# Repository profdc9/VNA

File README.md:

This a project to create a Vector Network Analyzer based on the EU1KY antenna tuner that can be reconfigured for different needs.  This material is copyrighted by Daniel Marks (KW4TI) and licensed under the Creative Commons License CC-BY-SA 4.0.  The software is licensed under the zlib license.  These are open source licenses that permit commercial use, modification and redistribution with attribution, and require licensees to assume all risk for using the copyrighted materials.

Currently what is on this github are the Kicad files for the VNA and the software.  The software uses the "stm32duino" extension to the Arduino IDE.  The Arduino IDE can be downloaded from

https://www.arduino.cc/en/Main/Software

The stm32duino software can be installed using the instructions on the stm32duino web site

https://github.com/rogerclarkmelbourne/Arduino_STM32/wiki/Installation

which involves (at this time) downloading the git archive for the stm32duino and placing it under the "hardware" folder in your Arduino folder.

There are several Arduino libraries that are required for the SI5351A frequency synthesizer chip, ILI9341 TFT display module, and XPT2046 touchscreen controller.  These are provided for your use under the "libraries" directory of this archive, but may not be the most recent versions.  You could copy these directories into the "libraries" folder in your Arduino directory.

---------------------------------

The VNA may be used with or without a touchscreen.  If a touchscreen it used, it should be compiled with the "VNA_TOUCHSCREEN" defined in VNA.h.  If you do not have a touchscreen, you can ground the pin PB13 and it will start up without a touchscreen, only appearing a USB CDC serial port device.  You can then type "HELP" to see the list of commands.

The touchscreen used is a 2.8" touchscreen with a SPI interface to the ILI9341 and XPT2046.  These are commonly available at a low price.  To connect it to the SPI interface connector header "J1" on the board, use a 14 pin IDC ribbon cable.

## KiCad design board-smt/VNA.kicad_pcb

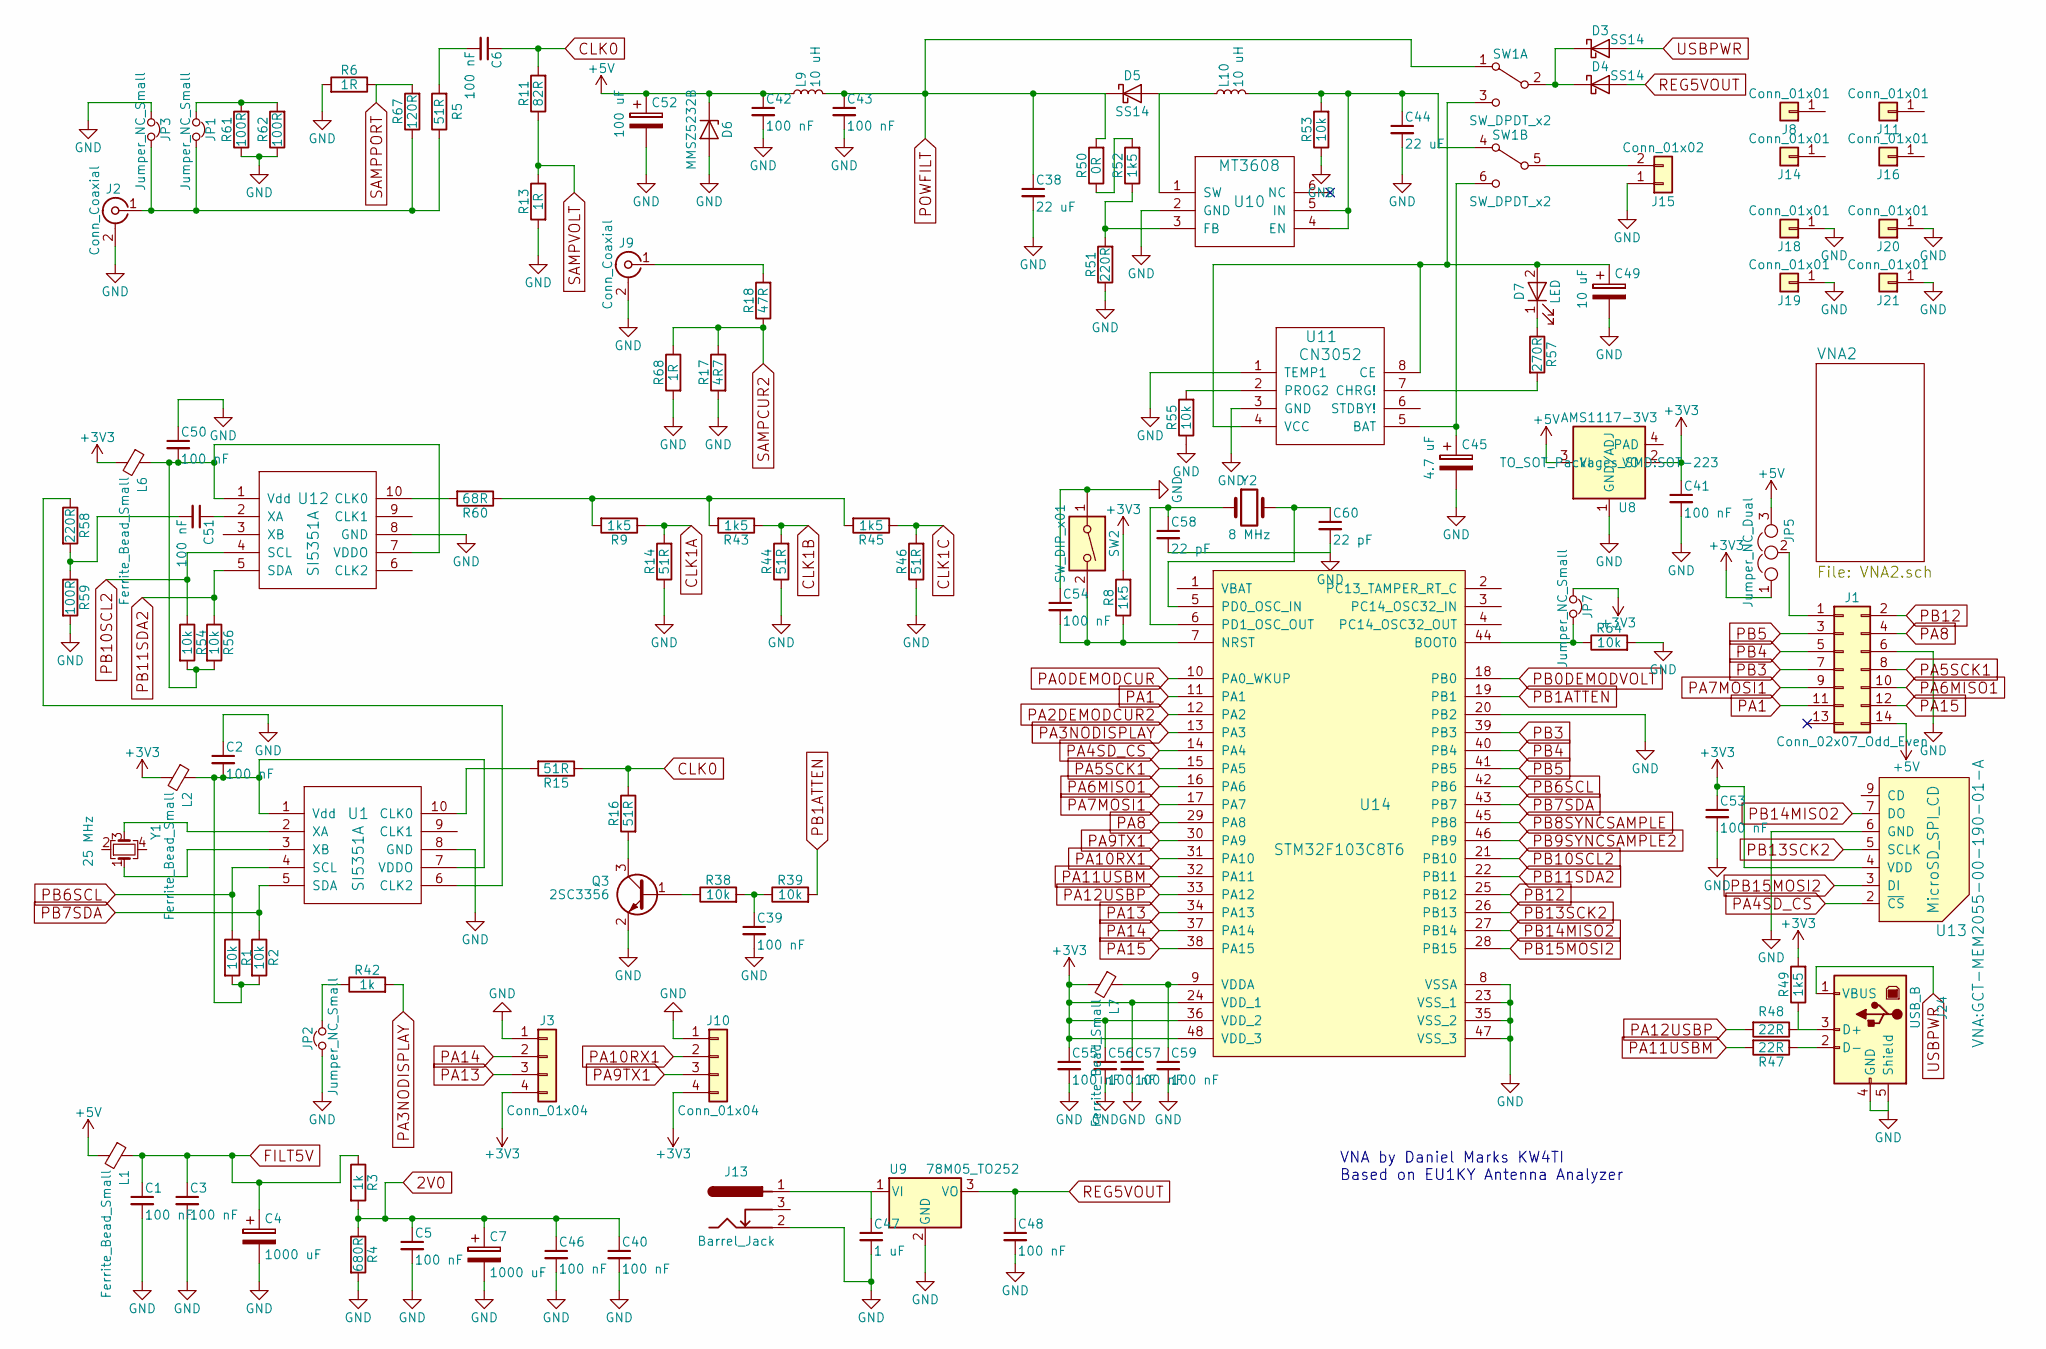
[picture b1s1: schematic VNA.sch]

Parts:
C1, C2, C3, C5, C6, C39, C40, C41, C42, C43, C46, C48, C50, C54, C55, C56, C57, C59: 100 nF; C_0805_HandSoldering; LCSC C49678
C4, C7: 1000 uF; CP_Elec_8x10.5
C38, C44: 22 uF; C_1210_HandSoldering
C45: 4.7 uF; CP_Elec_4x4.5
C47: 1 uF; C_0805_HandSoldering; LCSC C28323
C49: 10 uF; CP_Elec_4x4.5
C51, C53: 100 nF; C_0805_HandSoldering
C52: 100 uF; CP_Elec_4x4.5
C58, C60: 22 pF; C_0805_HandSoldering; LCSC C1804
D3, D4, D5: SS14; D_SMA; LCSC C2480
D6: MMSZ5232B; D_MiniMELF; LCSC C8062
D7: LED; LED_0805; LCSC C84256
J1: Conn_02x07_Odd_Even; Pin_Header_Straight_2x07_Pitch2.54mm
J2, J9: Conn_Coaxial; Amphenol_RF_SMA_132289
J3, J10: Conn_01x04; Pin_Header_Straight_1x04_Pitch2.54mm
J8, J11, J14, J16, J18, J19, J20, J21: Conn_01x01; 1pin
J13: Barrel_Jack; BARREL_JACK
J15: Conn_01x02; Molex_KK-6410-02_02x2.54mm_Straight
J24: USB_B
JP1, JP2, JP3, JP7: Jumper_NC_Small; Pin_Header_Straight_1x02_Pitch2.54mm
JP5: Jumper_NC_Dual; Pin_Header_Straight_1x03_Pitch2.54mm
L1, L2, L6, L7: Ferrite_Bead_Small; L_0805_HandSoldering; LCSC C1015
L9, L10: 10 uH; L_7.3x7.3_H4.5
Q3: 2SC3356; SOT-23; LCSC C9659
R1, R2, R38, R39, R53, R54, R55, R56, R64: 10k; R_0805_HandSoldering; LCSC C17414
R3, R42: 1k; R_0805_HandSoldering; LCSC C17513
R4: 680R; R_0805_HandSoldering; LCSC C17798
R5, R14, R15, R16, R44, R46: 51R; R_0805_HandSoldering; LCSC C17738
R6, R13, R68: 1R; R_0805_HandSoldering; LCSC C25271
R8, R9, R43, R45, R49, R52: 1k5; R_0805_HandSoldering; LCSC C4310
R11: 82R; R_0805_HandSoldering; LCSC C17841
R17: 4R7; R_0805_HandSoldering; LCSC C17675
R18: 47R; R_0805_HandSoldering; LCSC C17714
R47, R48: 22R; R_0805_HandSoldering; LCSC C17561
R50: 0R; R_0805_HandSoldering; LCSC C17477
R51, R58: 220R; R_0805_HandSoldering; LCSC C17557
R57: 270R; R_0805_HandSoldering; LCSC C17590
R59, R61, R62: 100R; R_0805_HandSoldering; LCSC C17408
R60: 68R; R_0805_HandSoldering; LCSC C17802
R67: 120R; R_0805_HandSoldering; LCSC C17437
SW1: SW_DPDT_x2; Molex_KK-6410-06_06x2.54mm_Straight
SW2: SW_DIP_x01; SW_PUSH_6mm
U1, U12: SI5351A; MSOP-10_3x3mm_Pitch0.5mm
U8: AMS1117-3V3; SOT-223; MPN LM1117; LCSC C6186
U9: 78M05_TO252; TO-252-3_TabPin2; LCSC C58069
U10: MT3608; SOT-23-6
U11: CN3052; TI_SO-PowerPAD-8
U13: MicroSD_SPI_CD; GCT-MEM2055-00-190-01-A
U14: STM32F103C8T6; LQFP-48_7x7mm_Pitch0.5mm; LCSC C8304
Y1: 25 MHz; Crystal_SMD_3225-4pin_3.2x2.5mm_HandSoldering; LCSC C9006
Y2: 8 MHz; Crystal_SMD_5032-2pin_5.0x3.2mm_HandSoldering; LCSC C115962

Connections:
2V0: C5.1, C7.1, C40.1, C46.1, R3.2, R4.1; also elsewhere on the board
+3V3: C41.1, C53.1, C55.1, C56.1, C57.1, J3.4, J10.4, JP5.1, JP7.1, L2.2, L6.2, L7.2, R8.2, R49.2, U8.2 (VO), U13.4 (VDD), U14.24 (VDD_1), U14.36 (VDD_2), U14.48 (VDD_3)
+5V: C42.1, C52.1, D6.1 (K), J1.14, JP5.3, L1.2, L9.1, U8.3 (VI)
CLK0: C6.1, R11.2, R15.1, R16.1
CLK1A: R9.1, R14.2; also elsewhere on the board
CLK1B: R43.1, R44.2; also elsewhere on the board
CLK1C: R45.1, R46.2; also elsewhere on the board
FILT5V: C1.1, C3.1, C4.1, L1.1, R3.1; also elsewhere on the board
GND: C1.2, C2.1, C3.2, C4.2, C5.2, C7.2, C38.2, C39.2, C40.2, C41.2, C42.2, C43.2, C44.2, C45.2, C46.2, C47.2, C48.2, C49.2, C50.1, C52.2, C53.2, C54.1, C55.2, C56.2, C57.2, C58.2, C59.2, C60.2, D6.2 (A), J1.6, J2.2 (Ext), J3.1, J9.2 (Ext), J10.1, J13.2, J15.1, J18.1, J19.1, J20.1, J21.1, J24.4 (GND), J24.5 (Shield), JP2.1, JP3.1, Q3.2 (E), R4.2, R6.2, R13.2, R14.1, R17.2, R44.1, R46.1, R51.1, R53.1, R55.1, R59.2, R61.1, R62.1, R64.2, R68.2, SW2.1, U1.8 (GND), U8.1 (GND/ADJ), U9.2 (GND), U10.2 (GND), U11.1 (TEMP1), U11.3 (GND), U12.8 (GND), U13.6 (GND), U14.8 (VSSA), U14.20 (PB2), U14.23 (VSS_1), U14.35 (VSS_2), U14.47 (VSS_3); also elsewhere on the board
unnamed: C2.2, L2.1, R1.2, R2.2, U1.1 (Vdd), U1.7 (VDDO)
unnamed: C6.2, R5.2
unnamed: C39.1, R38.2, R39.1
unnamed: C44.1, L10.2, R53.2, SW1.4 (A), U10.4 (EN), U10.5 (IN)
unnamed: C45.1, SW1.6 (C), U11.5 (BAT)
unnamed: C47.1, J13.1, U9.1 (VI)
unnamed: C49.1, D7.2 (A), SW1.3 (C), U11.4 (VCC), U11.8 (CE)
unnamed: C50.2, L6.1, R54.2, R56.2, U12.1 (Vdd), U12.7 (VDDO)
unnamed: C51.1, U12.2 (XA)
unnamed: C51.2, R58.2, R59.1
unnamed: C54.2, R8.1, SW2.2, U14.7 (NRST)
unnamed: C58.1, U14.6 (PD1_OSC_OUT), Y2.1
unnamed: C59.1, L7.1, U14.9 (VDDA)
unnamed: C60.1, U14.5 (PD0_OSC_IN), Y2.2
unnamed: D3.1 (K), D4.1 (K), SW1.2 (B)
unnamed: D5.2 (A), L10.1, U10.1 (SW)
unnamed: D7.1 (K), R57.1
unnamed: J1.1, JP5.2
unnamed: J2.1 (In), JP1.2, JP3.2, R5.1, R67.1
unnamed: J9.1 (In), R18.2
unnamed: J15.2, SW1.5 (B)
unnamed: J24.2 (D-), R47.1
unnamed: J24.3 (D+), R48.1, R49.1
unnamed: JP1.1, R61.2, R62.2
unnamed: JP2.2, R42.1
unnamed: JP7.2, R64.1, U14.44 (BOOT0)
unnamed: Q3.1 (B), R38.1
unnamed: Q3.3 (C), R16.2
unnamed: R15.2, U1.10 (CLK0)
unnamed: R9.2, R43.2, R45.2, R60.1
unnamed: R50.1, R52.2
unnamed: R51.2, R52.1, U10.3 (FB)
unnamed: R55.2, U11.2 (PROG2)
unnamed: R57.2, U11.7 (CHRG!)
unnamed: R58.1, U1.6 (CLK2)
unnamed: R60.2, U12.10 (CLK0)
unnamed: U1.2 (XA), Y1.3
unnamed: U1.3 (XB), Y1.1
PA0DEMODCUR: U14.10 (PA0_WKUP); also elsewhere on the board
PA1: J1.11, U14.11 (PA1)
PA2DEMODCUR2: U14.12 (PA2); also elsewhere on the board
PA3NODISPLAY: R42.2, U14.13 (PA3)
PA4SD_CS: U13.2 (~CS), U14.14 (PA4)
PA5SCK1: J1.8, U14.15 (PA5)
PA6MISO1: J1.10, U14.16 (PA6)
PA7MOSI1: J1.9, U14.17 (PA7)
PA8: J1.4, U14.29 (PA8)
PA9TX1: J10.3, U14.30 (PA9)
PA10RX1: J10.2, U14.31 (PA10)
PA11USBM: R47.2, U14.32 (PA11)
PA12USBP: R48.2, U14.33 (PA12)
PA13: J3.3, U14.34 (PA13)
PA14: J3.2, U14.37 (PA14)
PA15: J1.12, U14.38 (PA15)
PB0DEMODVOLT: U14.18 (PB0); also elsewhere on the board
PB1ATTEN: R39.2, U14.19 (PB1)
PB3: J1.7, U14.39 (PB3)
PB4: J1.5, U14.40 (PB4)
PB5: J1.3, U14.41 (PB5)
PB6SCL: R1.1, U1.4 (SCL), U14.42 (PB6)
PB7SDA: R2.1, U1.5 (SDA), U14.43 (PB7)
PB8SYNCSAMPLE: U14.45 (PB8); also elsewhere on the board
PB9SYNCSAMPLE2: U14.46 (PB9); also elsewhere on the board
PB10SCL2: R54.1, U12.4 (SCL), U14.21 (PB10)
PB11SDA2: R56.1, U12.5 (SDA), U14.22 (PB11)
PB12: J1.2, U14.25 (PB12)
PB13SCK2: U13.5 (SCLK), U14.26 (PB13)
PB14MISO2: U13.7 (DO), U14.27 (PB14)
PB15MOSI2: U13.3 (DI), U14.28 (PB15)
POWFILT: C38.1, C43.1, D5.1 (K), L9.2, R50.2, SW1.1 (A)
REG5VOUT: C48.1, D4.2 (A), U9.3 (VO)
SAMPCUR2: R17.1, R18.1, R68.1; also elsewhere on the board
SAMPPORT: R6.1, R67.2; also elsewhere on the board
SAMPVOLT: R11.1, R13.1; also elsewhere on the board
USBPWR: D3.2 (A), J24.1 (VBUS)

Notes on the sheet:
VNA by Daniel Marks KW4TI Based on EU1KY Antenna Analyzer

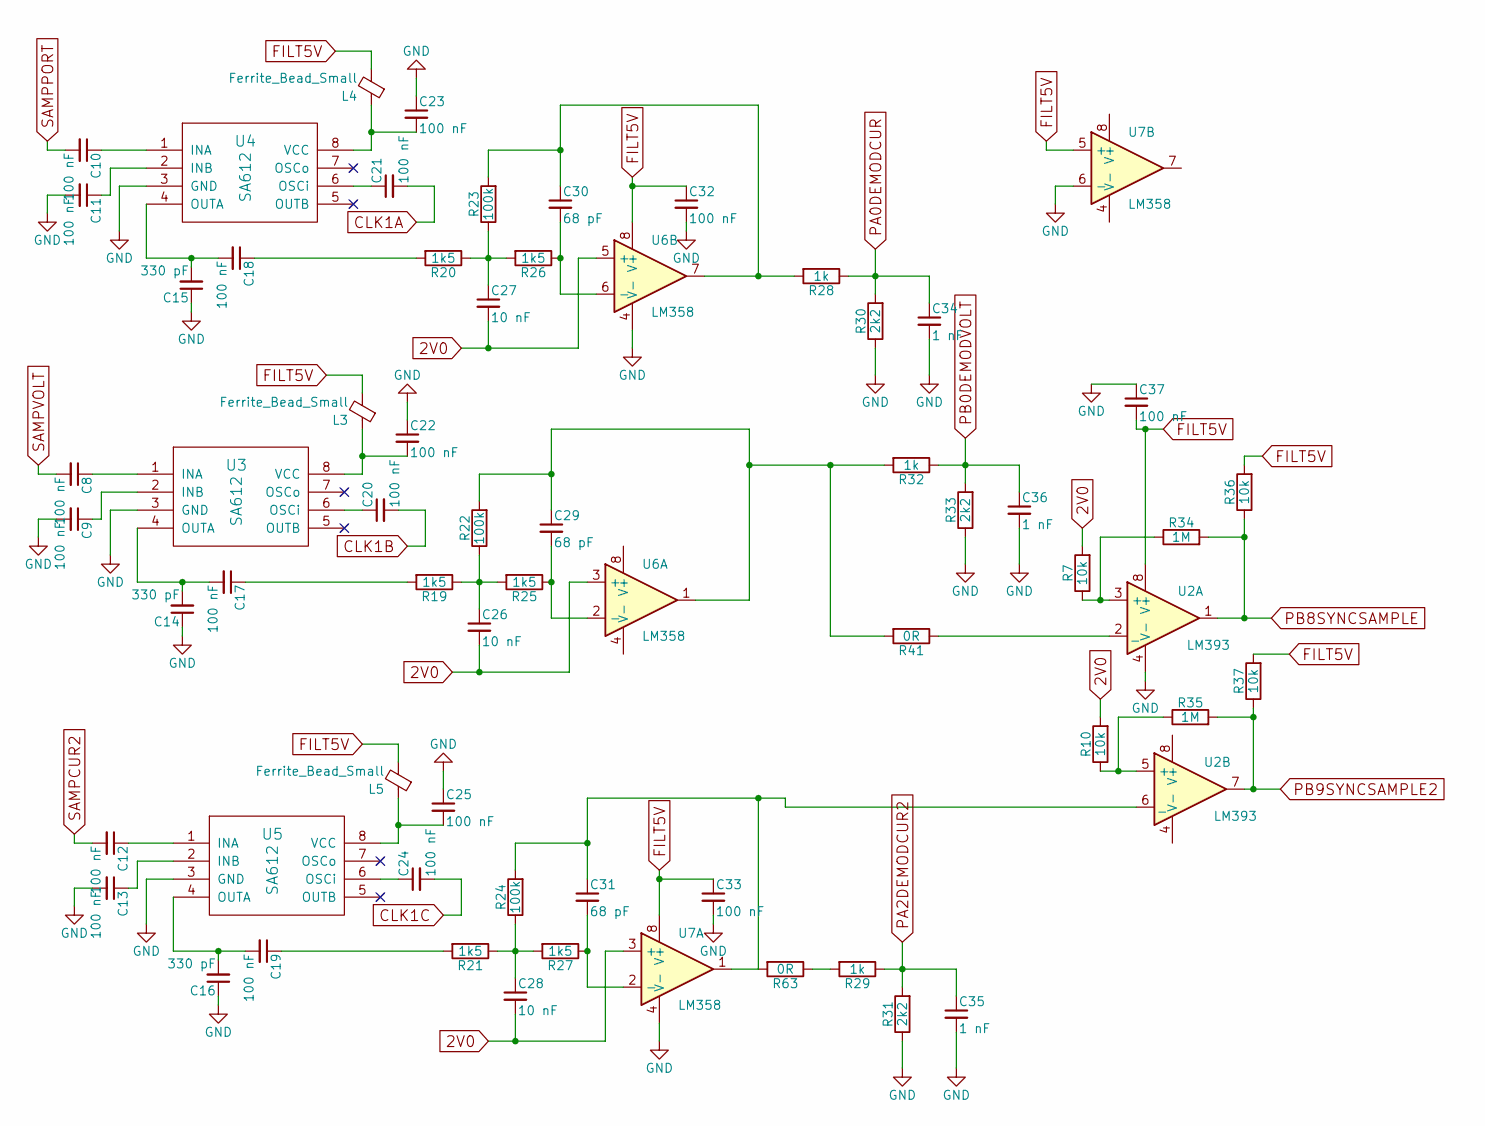
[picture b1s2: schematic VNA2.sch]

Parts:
C8, C9, C10, C11, C12, C13, C17, C18, C19, C20, C21, C22, C23, C24, C32, C33: 100 nF; C_0805_HandSoldering; LCSC C49678
C14, C15, C16: 330 pF; C_0805_HandSoldering; LCSC C51207
C25, C37: 100 nF; C_0805_HandSoldering
C26, C27, C28: 10 nF; C_0805_HandSoldering; LCSC C1710
C29, C30, C31: 68 pF; C_0805_HandSoldering; LCSC C1834
C34, C35, C36: 1 nF; C_0805_HandSoldering; LCSC C46653
L3, L4, L5: Ferrite_Bead_Small; L_0805_HandSoldering; LCSC C1015
R7, R10, R36, R37: 10k; R_0805_HandSoldering; LCSC C17414
R19, R20, R21, R25, R26, R27: 1k5; R_0805_HandSoldering; LCSC C4310
R22, R23, R24: 100k; R_0805_HandSoldering; LCSC C17407
R28, R29, R32: 1k; R_0805_HandSoldering; LCSC C17513
R30, R31, R33: 2k2; R_0805_HandSoldering; LCSC C17520
R34, R35: 1M; R_0805_HandSoldering; LCSC C17514
R41, R63: 0R; R_0805_HandSoldering; LCSC C17477
U2: LM393; SOIC-8_3.9x4.9mm_Pitch1.27mm; LCSC C7955
U3, U4, U5: SA612; SOIC-8_3.9x4.9mm_Pitch1.27mm
U6, U7: LM358; SOIC-8_3.9x4.9mm_Pitch1.27mm; LCSC C7950

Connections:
2V0: C26.2, C27.2, C28.2, R7.2, R10.2, U6.3 (+), U6.5 (+), U7.3 (+); also elsewhere on the board
CLK1A: C21.2; also elsewhere on the board
CLK1B: C20.2; also elsewhere on the board
CLK1C: C24.2; also elsewhere on the board
FILT5V: C32.1, C33.1, C37.2, L3.2, L4.2, L5.2, R36.2, R37.2, U2.8 (V+), U6.8 (V+), U7.5 (+), U7.8 (V+); also elsewhere on the board
GND: C9.2, C11.2, C13.2, C14.1, C15.1, C16.1, C22.1, C23.1, C25.1, C32.2, C33.2, C34.2, C35.2, C36.2, C37.1, R30.1, R31.1, R33.1, U2.4 (V-), U3.3 (GND), U4.3 (GND), U5.3 (GND), U6.4 (V-), U7.4 (V-), U7.6 (-); also elsewhere on the board
unnamed: C8.1, U3.1 (INA)
unnamed: C9.1, U3.2 (INB)
unnamed: C10.1, U4.1 (INA)
unnamed: C11.1, U4.2 (INB)
unnamed: C12.1, U5.1 (INA)
unnamed: C13.1, U5.2 (INB)
unnamed: C14.2, C17.2, U3.4 (OUTA)
unnamed: C15.2, C18.2, U4.4 (OUTA)
unnamed: C16.2, C19.2, U5.4 (OUTA)
unnamed: C17.1, R19.2
unnamed: C18.1, R20.2
unnamed: C19.1, R21.2
unnamed: C20.1, U3.6 (OSCi)
unnamed: C21.1, U4.6 (OSCi)
unnamed: C22.2, L3.1, U3.8 (VCC)
unnamed: C23.2, L4.1, U4.8 (VCC)
unnamed: C24.1, U5.6 (OSCi)
unnamed: C25.2, L5.1, U5.8 (VCC)
unnamed: C26.1, R19.1, R22.1, R25.2
unnamed: C27.1, R20.1, R23.1, R26.2
unnamed: C28.1, R21.1, R24.1, R27.2
unnamed: C29.1, R22.2, R32.2, R41.2, U6.1
unnamed: C29.2, R25.1, U6.2 (-)
unnamed: C30.1, R23.2, R28.2, U6.7
unnamed: C30.2, R26.1, U6.6 (-)
unnamed: C31.1, R24.2, R63.2, U2.6 (_), U7.1
unnamed: C31.2, R27.1, U7.2 (-)
unnamed: R10.1, R35.1, U2.5 (+)
unnamed: R29.2, R63.1
unnamed: R7.1, R34.1, U2.3 (+)
unnamed: R41.1, U2.2 (_)
PA0DEMODCUR: C34.1, R28.1, R30.2; also elsewhere on the board
PA2DEMODCUR2: C35.1, R29.1, R31.2; also elsewhere on the board
PB0DEMODVOLT: C36.1, R32.1, R33.2; also elsewhere on the board
PB8SYNCSAMPLE: R34.2, R36.1, U2.1; also elsewhere on the board
PB9SYNCSAMPLE2: R35.2, R37.1, U2.7; also elsewhere on the board
SAMPCUR2: C12.2; also elsewhere on the board
SAMPPORT: C10.2; also elsewhere on the board
SAMPVOLT: C8.2; also elsewhere on the board

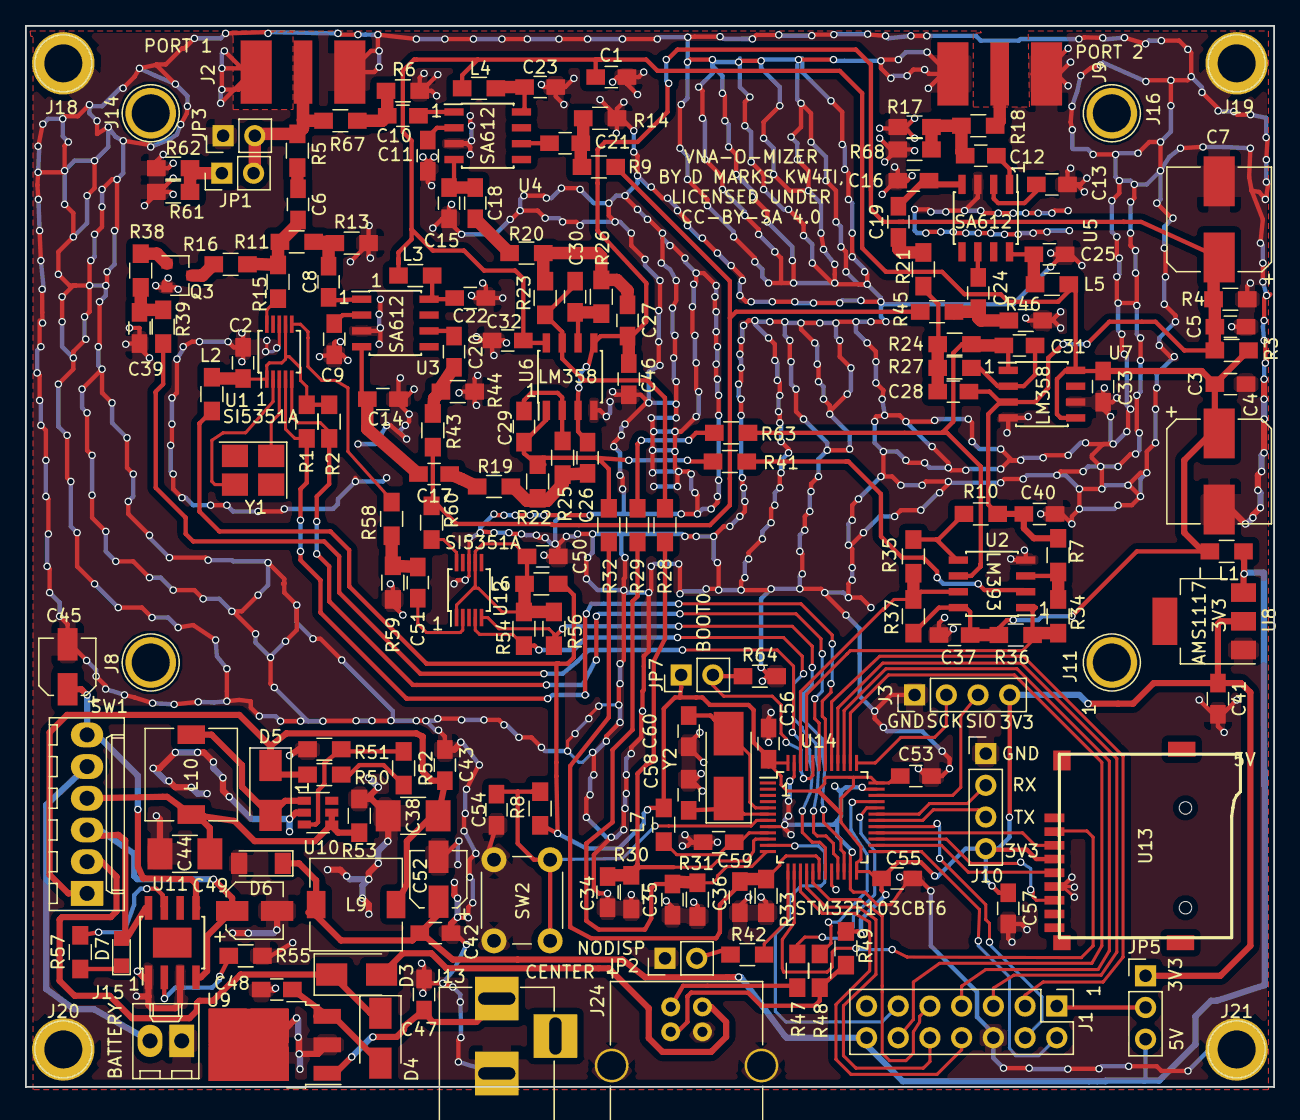
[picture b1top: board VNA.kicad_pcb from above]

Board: 2 copper layers, 100.0 x 85.0 mm, 178 parts (0 on the bottom side), 115 nets.

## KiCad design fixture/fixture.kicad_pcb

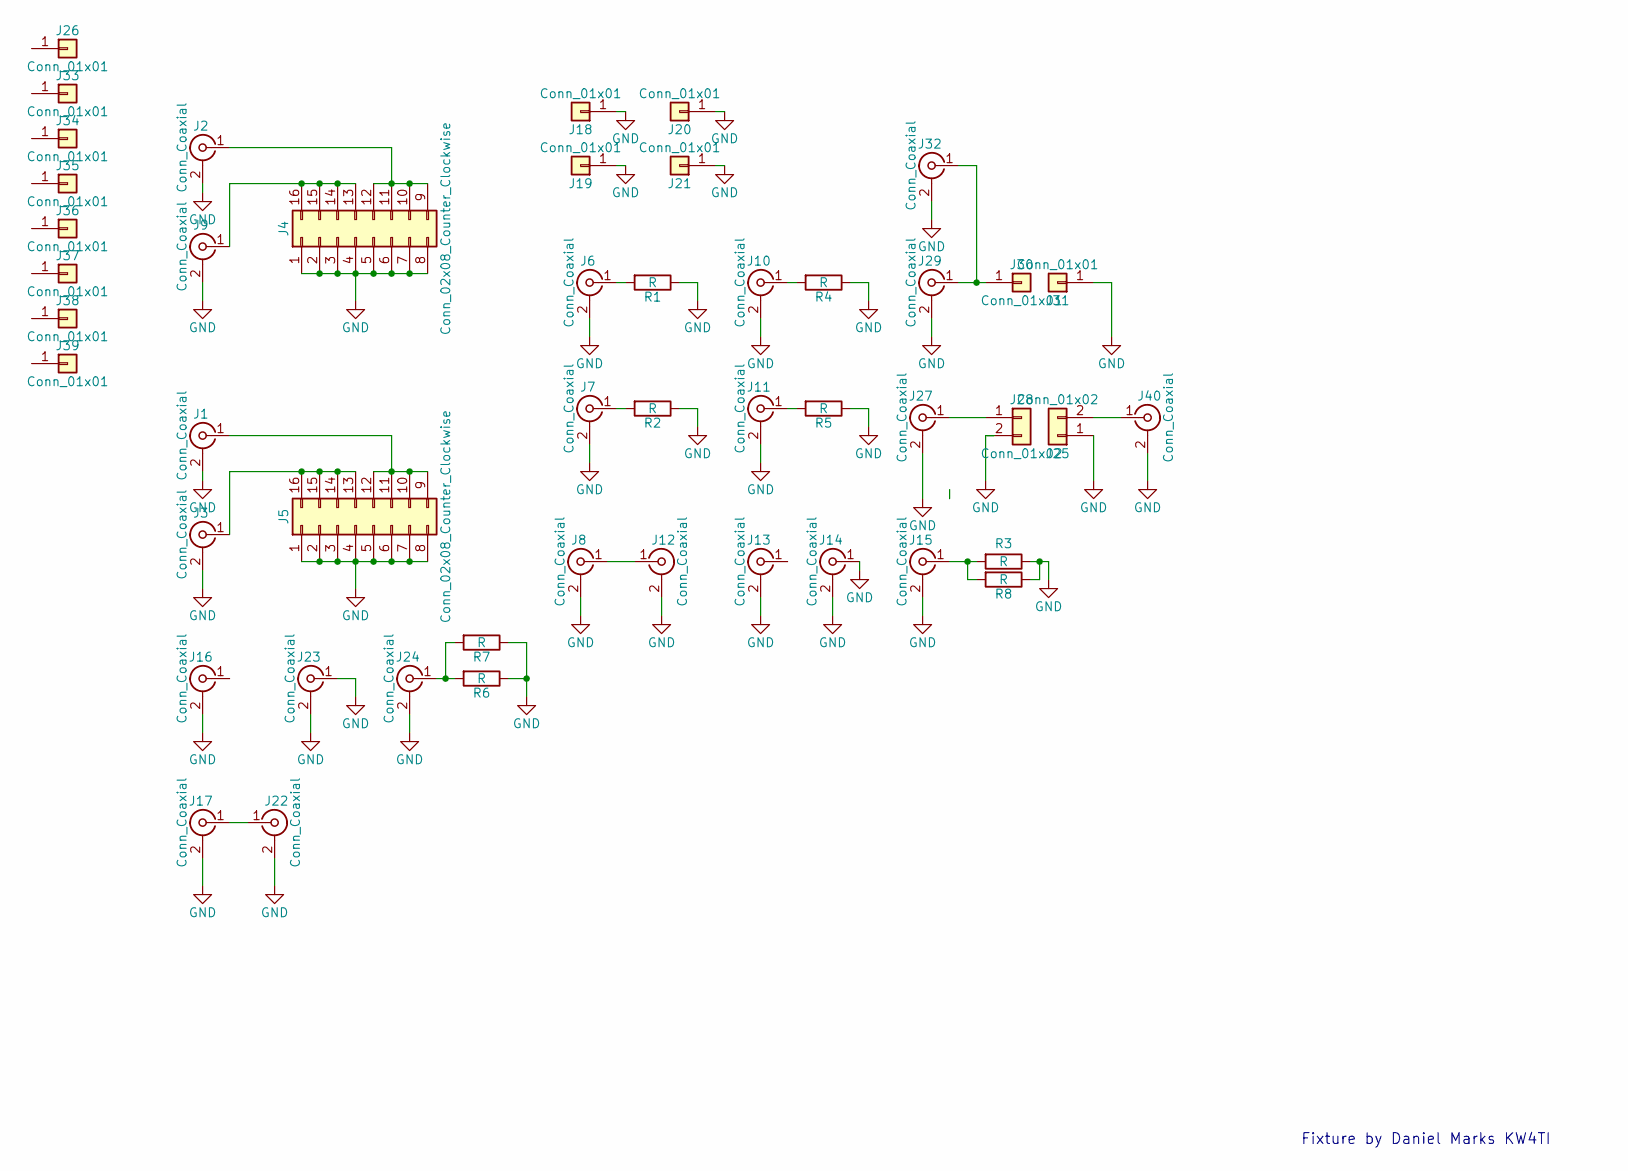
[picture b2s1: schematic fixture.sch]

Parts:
J1, J3, J16, J17, J22, J23, J24, J32: Conn_Coaxial; bnc-ci
J2, J6, J7, J8, J9, J10, J11, J12, J13, J14, J15, J27, J29, J40: Conn_Coaxial; Amphenol_RF_SMA_132289
J4, J5: Conn_02x08_Counter_Clockwise; ZIFSocket16pin
J18, J19, J20, J21, J30, J31: Conn_01x01; 1pin
J25, J28: Conn_01x02; TerminalBlock_bornier-2_P5.08mm
J26, J33, J34, J35, J36, J37, J38, J39: Conn_01x01; AirHole
R1, R2, R3, R4, R5, R6, R7, R8: R; R_0805_HandSoldering

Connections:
GND: J1.2 (Ext), J2.2 (Ext), J3.2 (Ext), J4.1, J4.2, J4.3, J4.4, J4.5, J4.6, J4.7, J4.8, J5.1, J5.2, J5.3, J5.4, J5.5, J5.6, J5.7, J5.8, J6.2 (Ext), J7.2 (Ext), J8.2 (Ext), J9.2 (Ext), J10.2 (Ext), J11.2 (Ext), J12.2 (Ext), J13.2 (Ext), J14.1 (In), J14.2 (Ext), J15.2 (Ext), J16.2 (Ext), J17.2 (Ext), J18.1, J19.1, J20.1, J21.1, J22.2 (Ext), J23.1 (In), J23.2 (Ext), J24.2 (Ext), J25.1, J27.2 (Ext), J28.2, J29.2 (Ext), J31.1, J32.2 (Ext), J40.2 (Ext), R1.1, R2.1, R3.1, R4.1, R5.1, R6.1, R7.1, R8.1
unnamed: J1.1 (In), J5.9, J5.10, J5.11, J5.12
unnamed: J2.1 (In), J4.9, J4.10, J4.11, J4.12
unnamed: J3.1 (In), J5.13, J5.14, J5.15, J5.16
unnamed: J4.13, J4.14, J4.15, J4.16, J9.1 (In)
unnamed: J6.1 (In), R1.2
unnamed: J7.1 (In), R2.2
unnamed: J10.1 (In), R4.2
unnamed: J11.1 (In), R5.2
unnamed: J8.1 (In), J12.1 (In)
unnamed: J15.1 (In), R3.2, R8.2
unnamed: J17.1 (In), J22.1 (In)
unnamed: J24.1 (In), R6.2, R7.2
unnamed: J25.2, J40.1 (In)
unnamed: J27.1 (In), J28.1
unnamed: J29.1 (In), J30.1, J32.1 (In)

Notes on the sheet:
Fixture by Daniel Marks KW4TI

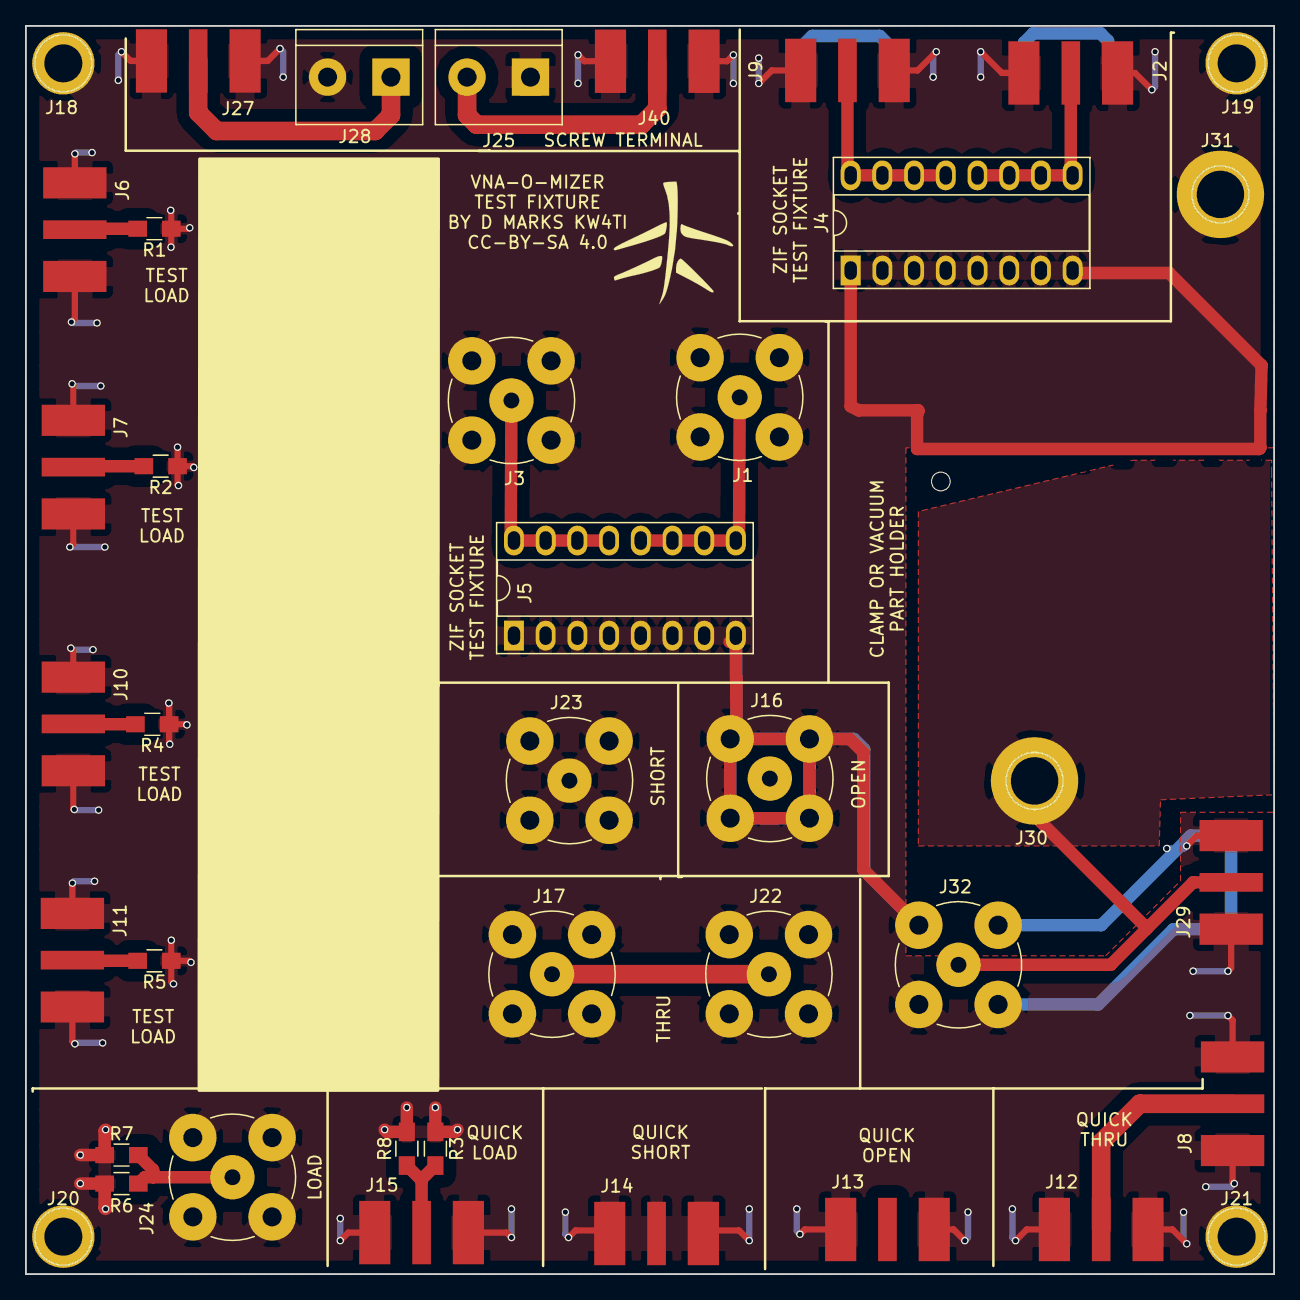
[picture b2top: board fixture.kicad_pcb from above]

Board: 2 copper layers, 100.0 x 100.0 mm, 48 parts (0 on the bottom side), 16 nets.

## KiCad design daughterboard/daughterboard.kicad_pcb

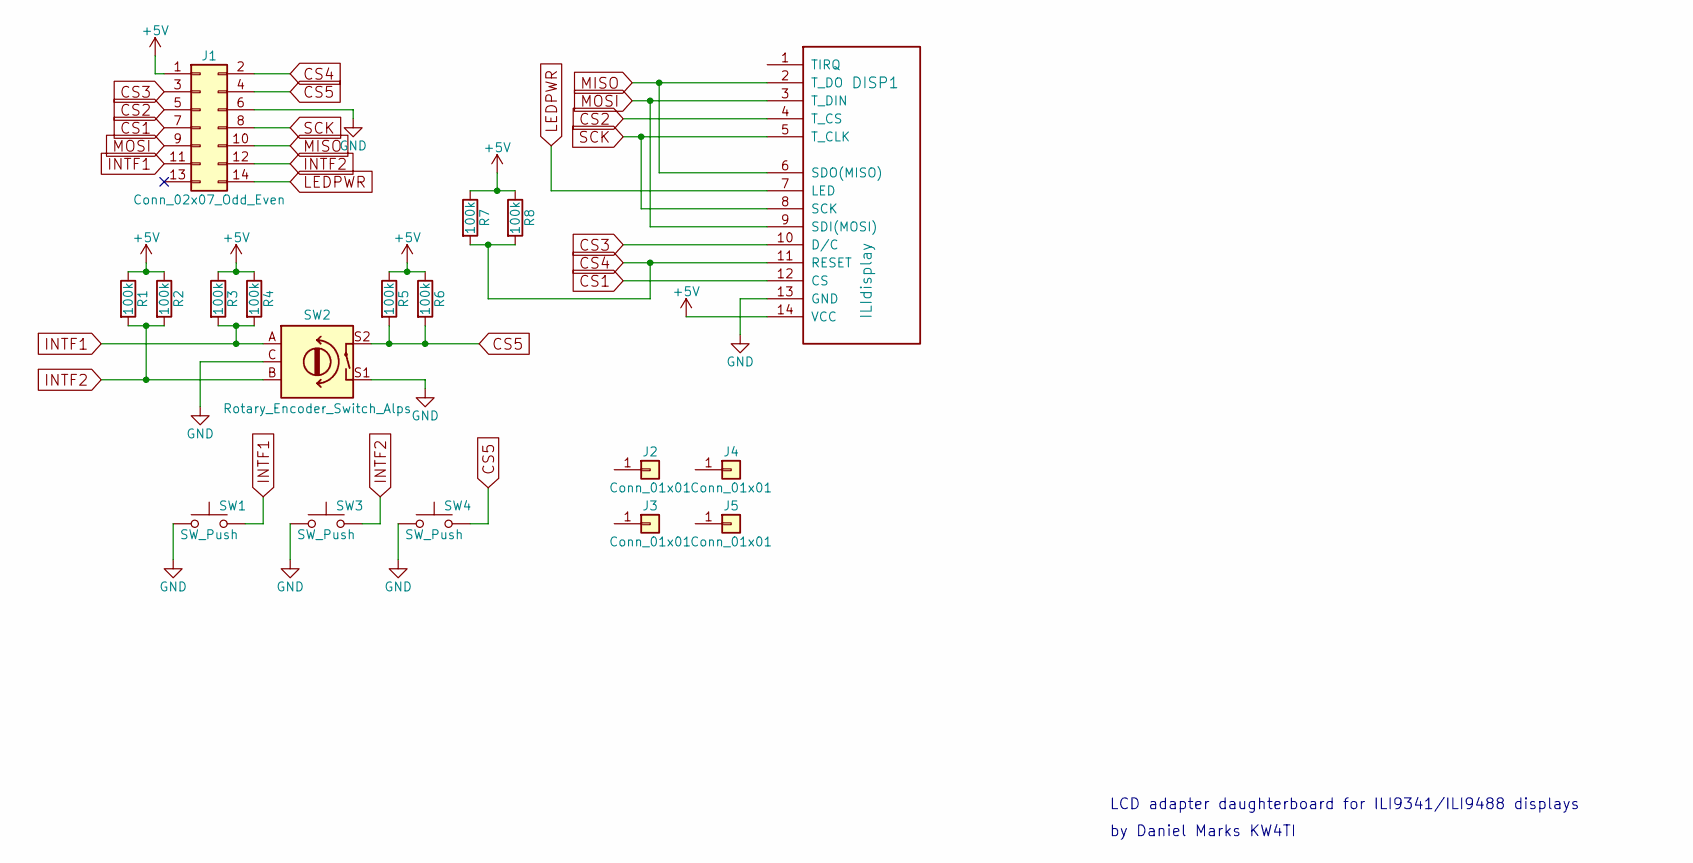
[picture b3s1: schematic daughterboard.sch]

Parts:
DISP1: ILIdisplay; Pin_Header_Straight_1x14_Pitch2.54mm
J1: Conn_02x07_Odd_Even; Pin_Header_Straight_2x07_Pitch2.54mm
J2, J3, J4, J5: Conn_01x01; 1pin
R1, R3, R5, R7: 100k; R_0805_HandSoldering
R2, R4, R6, R8: 100k; R_Axial_DIN0207_L6.3mm_D2.5mm_P7.62mm_Horizontal
SW1, SW3, SW4: SW_Push; SW_PUSH_6mm
SW2: Rotary_Encoder_Switch_Alps; RotaryEncoder_Alps_EC11E-Switch_Vertical_H20mm

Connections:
+5V: DISP1.14 (VCC), J1.1, R1.1, R2.1, R3.1, R4.1, R5.1, R6.1, R7.1, R8.1
CS1: DISP1.12 (CS), J1.7
CS2: DISP1.4 (T_CS), J1.5
CS3: DISP1.10 (D/C), J1.3
CS4: DISP1.11 (RESET), J1.2, R7.2, R8.2
CS5: J1.4, R5.2, R6.2, SW2.S2, SW4.2
GND: DISP1.13 (GND), J1.6, SW1.1, SW2.C, SW2.S1, SW3.1, SW4.1
INTF1: J1.11, R3.2, R4.2, SW1.2, SW2.A
INTF2: J1.12, R1.2, R2.2, SW2.B, SW3.2
LEDPWR: DISP1.7 (LED), J1.14
MISO: DISP1.2 (T_DO), DISP1.6 (SDO(MISO)), J1.10
MOSI: DISP1.3 (T_DIN), DISP1.9 (SDI(MOSI)), J1.9
SCK: DISP1.5 (T_CLK), DISP1.8 (SCK), J1.8

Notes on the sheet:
LCD adapter daughterboard for ILI9341/ILI9488 displays
by Daniel Marks KW4TI

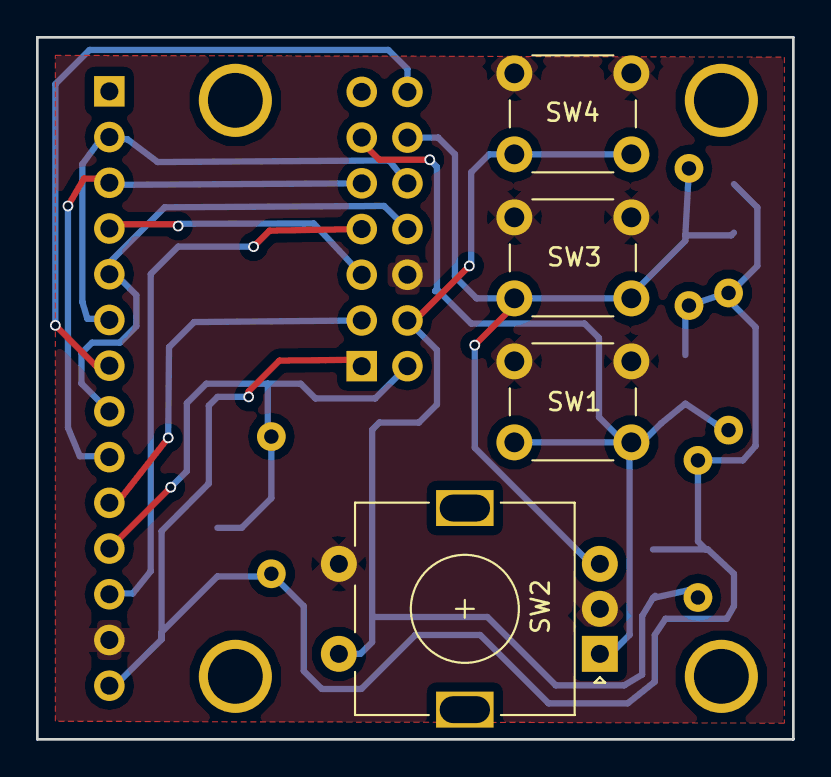
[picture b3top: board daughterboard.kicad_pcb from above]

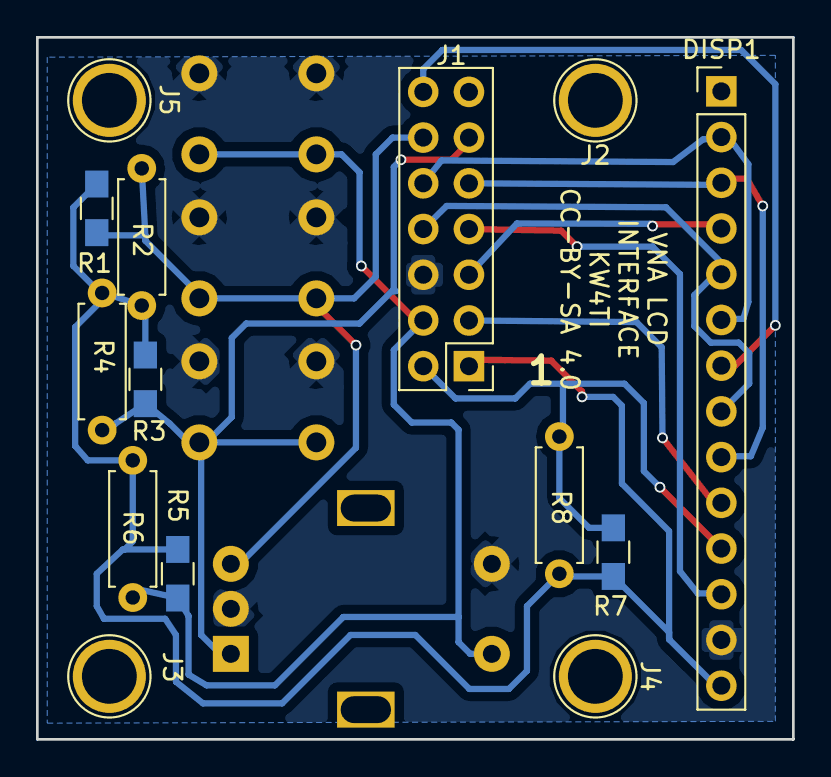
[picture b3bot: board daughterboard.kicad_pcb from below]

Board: 2 copper layers, 42.0 x 39.0 mm, 18 parts (14 on the bottom side), 13 nets.

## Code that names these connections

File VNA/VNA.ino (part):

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#include "touchscreen.h"
#endif

#define IFCLOCK_PIN PB8
#define IFCLOCK_PORT2_PIN PB9
#define AD_CUR_PIN PA0
#define AD_VOLT_PIN PB0
#define AD_CUR2_PIN PA2
#define ATTEN_PIN PB1
#define TOUCHSCREEN_DISABLE_PIN PA3

#ifdef VNA_TOUCHSCREEN
bool touchscreen_enabled;
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
void setup_pins(void)
{
  afio_cfg_debug_ports(AFIO_DEBUG_SW_ONLY); // release PB3 and PB5

  pinMode(ATTEN_PIN, OUTPUT);
  digitalWrite(ATTEN_PIN, LOW);
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
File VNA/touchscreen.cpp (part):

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#include "touchscreen.h"

// For the Adafruit shield, these are the default.
#define TFT_DC PB10
#define TFT_CS PB8
#define TFT_RESET PB12

#define XPT2046_CS PB9

XPT2046_Touchscreen ts(XPT2046_CS);
Adafruit_ILI9341_STM tft = Adafruit_ILI9341_STM(TFT_CS, TFT_DC, TFT_RESET);
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
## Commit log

2018-10-07 Made continuous ground plane over most of the part
2018-11-07 Removed useless parts of the board and make some corrections
2018-11-09 Added LCD mount
2018-11-13 Update schematic file
2018-11-20 Substitute LM339 for 74HC14
2018-11-20 First software that can read AD
2018-11-27 Working 1 and 2 port calibration
2018-12-01 JLCPCB order 2018-12-01
2018-12-07 Load and Save on Flash
2018-12-10 Working save to flash, 1 and 2 port, new design
2018-12-10 Sign error mistake in phase
2018-12-12 Clarified copyright of PCB, CC-BY-SA 4.0 and code which is zlib
2018-12-19 Added ILI9341 Touchscreen Support
2018-12-19 README.md didnt get committed for some reason
2018-12-19 Try again...
2018-12-20 Added some more CS pins to header
2018-12-21 Added Smith Chart plot
2018-12-22 Changed TL082 to LM358, other corrections to software
2018-12-24 A few minor fixes, grounding, etc.
2018-12-26 Added attenuation option to touchscreen, fixed attenuation resistors
2018-12-27 Added cursors to graphs and shunt impedance measurement mode
2018-12-28 Added ground connections
2018-12-29 Added surface mount version
2018-12-29 Fixed a label
2018-12-29 Added SMT board
2019-01-06 Added support for minimal minivna compatibility
2019-01-15 Reset PLL before each frequency change for maximum repeatability
2019-01-22 Changed frequency on X 3 mode to be higher (15 kHz)
2019-03-30 Added dual serial console support
2019-03-31 Decreased sensitivity of screen
2019-05-19 Removed unneded file from board-smit
2019-07-03 Changed SMA connector, added dual power option for LCD
2019-07-13 Turned a voltage regulator around
2019-09-30 Increased isolation between ports
2019-09-30 Mask removal on wrong layer
2019-10-02 Rearranged some more to reduce crosstalk
2019-10-02 Added even more isolation
2019-10-02 Added ferrite beads to serial connection
2019-10-02 Rearranged for shorter high frequency traces
2019-10-10 Ensured up-to-date gerber
2019-10-10 Added extra outputs to connector, changed display off pin
2019-10-23 Daughterboard added for jog wheel and buttons
2019-10-23 Added daughterboard for mounting LCD and jog wheel
2019-10-23 Created fixture PCB for calibration and component testing
2019-10-23 Added area around open circuit without copper fill
2019-10-23 Oops forgot to fill under screw clamp
2019-10-23 Made more room for handle of ZIF socket
2019-10-23 Moved mounting holes to ensure no interference
2019-10-23 Added debouncing capacitors
2019-10-23 Added resistors in discharge debounce
2019-10-23 Changed fixture to use toggle clamp
2019-10-26 Added vacuum holes to fixture
2019-10-26 Added many features:
    Calibration frequencies now separate from scan frequencies
    Bigger buttons
    Sideways Text in graphs
    Graphs now have a longer marker line
2019-10-27 Added spot measurement feature, extended to 600 MHz
2019-10-27 Moved the SI5351A even closer
2019-10-28 JLCPCB order 2019-10-27
2019-11-09 Modified fixture for larger holes for ZIF socket
2019-11-11 Added jogwheel and sweep, simplified daughterboard
2019-11-11 VNA-o-mizer is rechristened, added two files jogwheel.*
2019-11-11 Oops changed back to TIMER2
2019-11-13 Added JST 2.54 power and USB-B connecotrs
2019-11-13 oops silkscreening error
2019-11-14 Changed fixture loads to have less capacitance
2019-11-14 Added mt3608 boost converter for battery usage
2019-11-14 100 uH in pi filter
2019-11-14 Rearranged the PCB, CN3502 battery charger and MT3608 boost converter on-board
2019-11-16 Move components around on board, adjusted fixture, added touchscreen disables
2019-11-17 Rearranged some traces on board-smt for better isolation
2019-11-17 Added protection Zener diode on Pi filter to protect against ON/OFF transients
2019-11-20 Added provision for separate SI5351A for LO signal
2019-11-20 Cleaned up ground traces a bit
2019-11-20 Slaved the second SI5351A to the first SI5351A
2019-11-21 Moved jumper a little for lower parasitics
2019-11-22 JLCPCB order 2019-11-22
2019-11-26 Added VNA-O-MIZER Logo
2019-11-28 Tweaked the layout on port 2
2019-12-02 Fixed crystal pinout, added heatsink pad to CN3052A
2019-12-02 Fixed a few more outstanding issues
2019-12-05 Changed Schottky diode to SS14 and 1N4148 to BAV99
2019-12-05 Added source termination resistor to LO SI5351A
2020-01-13 Changes to finalize two SI5351A solution
2020-01-14 Shrank the SMT board by 15 mm
2020-01-14 Made a little space around external connectors
2020-01-17 Modified VNA code for two SI5351A
2020-01-18 Moved mounting holes slightly
2020-01-21 Bigger footprint for C4
2020-01-21 Updated Schematic
2020-01-23 Changed pullup resistors to 10k for less supply noise
2020-01-24 Updated software to add cursor for smith chart, also changed edge of triggering
2020-01-31 Put USB back through filter again
2020-02-04 Forgot VNAOMizer logo
2020-04-12 VNA-O-Mizer 1.0
2020-04-15 Added SD card slot, reorganized pins
2020-05-06 Adds SD card support, which is mandatory. Also changed firmware for new pinouts.
2020-05-06 Removed accidental inclusion of VNA in libraries directory
2020-05-28 Finally removed the bluepill!
2020-06-07 Choke bridge
2020-06-09 Changed to resistive bridge
2020-07-13 Submitted to JLCPCB 2020-07-12
2021-01-02 Modified some component values on bridge for better performance

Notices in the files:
VNA/VNA.ino:
Copyright (c) 2018 Daniel Marks
board-smt/VNA.kicad_pcb:
BY D MARKS KW4TI,
LICENSED UNDER
CC-BY-SA 4.0
